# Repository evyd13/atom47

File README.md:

# Atom47

This is the repository for the Atom47. At the moment you'll find Revision 4 AND 5 of the PCB, the final plate file and a design for a 3d printed case.

The Apache2 license apply to all of these works.

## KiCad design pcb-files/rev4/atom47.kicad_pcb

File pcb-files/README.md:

# Atom47 PCB

## Rev5 (with per key RGB)

## Rev4

### JLCPCB order process 

JLCPCB-specific production files can be found in [this folder](/pcb-files/rev4/manufacturing/jlc). Here are the files you need to upload to JLCPCB:

- `atom47-rev4-gerber.zip` 
- `Atom47-Rev4-BOM-JLC.csv` is the BOM (Bill of Materials) file
- `Atom47-Rev4-Bottom-CPL-JLC.csv` is the POS/CPL (Footprint POSition/Component Placement List) file

Once you have the files ready, go to the JLCPCB website and follow the steps below:

1. Upload the gerber file
2. Once it is processed, select the options for the PCB:
   1. Leave all options as default, choose your material and color etc.
   2. Remember that MOQ (Minimum Order Quantity) is `5` PCBs
   3. Set `Confirm Production file` to `Yes`
   4. Enable `PCB Assembly`
   5. Choose `Assemble bottom side`
   6. Leave all options as default, set `Confirm Parts Placement` to `Yes`
   7. Proceed with your order
3. Upload the BOM and CPL files
4. Once the files are uploaded, the system will automatically recognize the components and you will be able to review them:
   1. `ATMEGA32U2` is likely to be out of stock. You can choose the `Do not place` option and source it yourself, then finish assembly by hand 
5. Once the parts list is confirmed, the system will attempt to automatically place the components on the board. The initial placement will be off, but JLCPCB engineers will catch it and fix it for you. You can then review the corrected placement and confirm it later
6. Complete your order:
   1. Pay for production, choose your shipping option etc.
7. Your files will be reviewed by JLCPCB engineers, and you will have to confirm the corrected placement. Here's a preview of the verified, corrected placement:

*Note: MCU not seen here, as this component was out of stock at the time of this order. It was sourced separately, and the assembly was finished by hand*

8. Once you receive your PCBs, you can then proceed with testing, assembly (if needed) and flashing the firmware

### VIA support 

Follow these step to use your Rev4 Atom47 PCB with VIA:

1. Compile the firmware with VIA support using your preferred method
   1. Example: `qmk compile -kb evyd13/atom47 -km via`
2. Flash the firmware using your preferred method
3. Open VIA: 
   1. Navigate to the `Design` tab
   2. Click on `Load` under `Load Draft Definition`
   3. Provide the `Atom47_Rev4.json` file from [this folder](/pcb-files/rev4/via) 
4. Connect your Rev4 Atom47 PCB 

*Note: This definition file only supports the default Vortex Core layout*

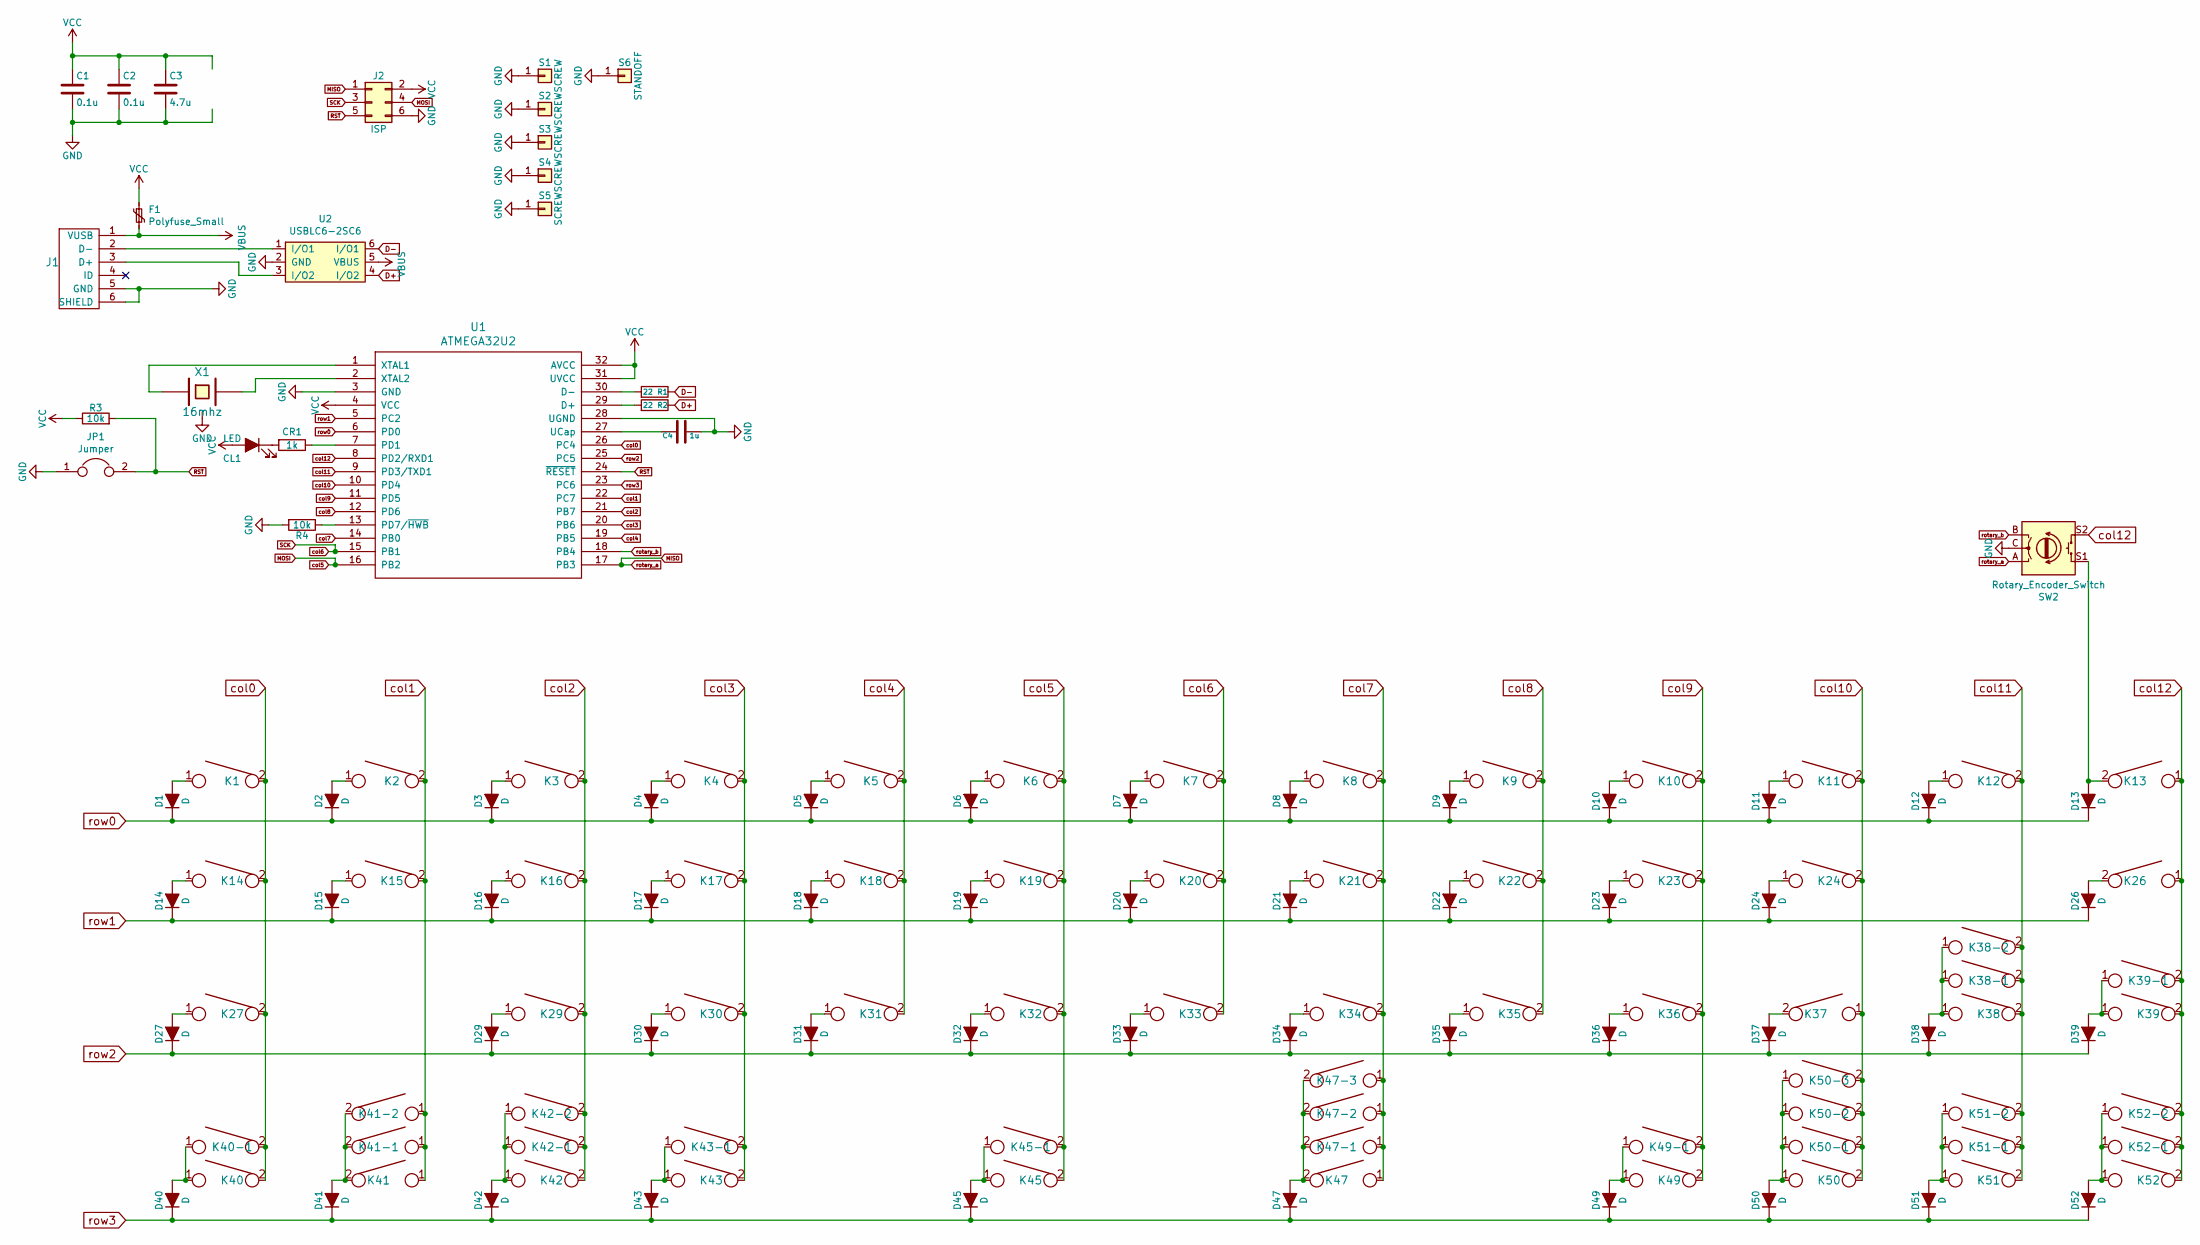
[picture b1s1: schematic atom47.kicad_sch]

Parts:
C1, C2: 0.1u; C_0603
C3: 4.7u; C_0603
C4: 1u; C_0603
CL1: LED; LED_0805
CR1: 1k; R_0603
D1, D2, D3, D4, D5, D6, D7, D8, D9, D10, D11, D12, D13, D14, D15, D16, D17, D18, D19, D20, D21, D22, D23, D24, D26, D27, D29, D30, D31, D32, D33, D34, D35, D36, D37, D38, D39, D40, D41, D42, D43, D45, D47, D49, D50, D51, D52: D; D_0805
F1: Polyfuse_Small; R_0603
J1: USB_mini_micro_B; U-F-M5DD-Y-L
J2: ISP; isp_standard
JP1: Jumper; reset
K1, K2, K3, K4, K5, K6, K7, K8, K9, K10, K11, K12, K13, K15, K16, K17, K18, K19, K20, K21, K22, K23, K24, K29, K30, K31, K32, K33, K34, K35, K36, K37, K38-2, K39, K41, K42, K42-2, K43, K43-1, K49, K49-1, K50, K50-1, K51, K51-1, K52-1: KEYSW; CHERRY_PLATE_100H
K14, K38, K39-1, K40, K41-1, K42-1, K50-3, K51-2, K52: KEYSW; CHERRY_PLATE_125H
K26, K27, K45, K45-1: KEYSW; CHERRY_PLATE_175H
K38-1: KEYSW; CHERRY_PLATE_225H
K40-1, K41-2, K50-2, K52-2: KEYSW; CHERRY_PLATE_150H
K47: KEYSW; CHERRY_PLATE_275H
K47-1: KEYSW; CHERRY_PLATE_625H
K47-2: KEYSW; CHERRY_PLATE_700H
K47-3: KEYSW; CHERRY_PLATE_200H
R1, R2: 22; R_0603
R3, R4: 10k; R_0603
S1, S2, S3, S4, S5: SCREW; Vortex_Core_screw
S6: STANDOFF; vortex_standoff
SW2: Rotary_Encoder_Switch; RotaryEncoder_Alps_EC11
U1: ATMEGA32U2
U2: USBLC6-2SC6
X1: 16mhz; Resonator_SMD_muRata_CSTNExxV-3Pin-p1.2

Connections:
D+: R2.1, U2.4 (I/O2)
D-: R1.1, U2.6 (I/O1)
GND: C1.2, C2.2, C3.2, C4.2, J1.5 (GND), J1.6 (SHIELD), J2.6, JP1.1, R4.2, S1.1, S2.1, S3.1, S4.1, S5.1, S6.1, SW2.C, U1.3 (GND), U1.28 (UGND), U2.2 (GND), X1.3
MISO: J2.1, SW2.A, U1.17 (PB3)
MOSI: J2.4, K6.2, K19.2, K32.2, K45.2, K45-1.2, U1.16 (PB2)
unnamed: C4.1, U1.27 (UCap)
unnamed: CL1.1 (K), CR1.2
unnamed: CR1.1, U1.7 (PD1)
unnamed: D1.2 (A), K1.1
unnamed: D2.2 (A), K2.1
unnamed: D3.2 (A), K3.1
unnamed: D4.2 (A), K4.1
unnamed: D5.2 (A), K5.1
unnamed: D6.2 (A), K6.1
unnamed: D7.2 (A), K7.1
unnamed: D8.2 (A), K8.1
unnamed: D9.2 (A), K9.1
unnamed: D10.2 (A), K10.1
unnamed: D11.2 (A), K11.1
unnamed: D12.2 (A), K12.1
unnamed: D13.2 (A), K13.2, SW2.S1
unnamed: D14.2 (A), K14.1
unnamed: D15.2 (A), K15.1
unnamed: D16.2 (A), K16.1
unnamed: D17.2 (A), K17.1
unnamed: D18.2 (A), K18.1
unnamed: D19.2 (A), K19.1
unnamed: D20.2 (A), K20.1
unnamed: D21.2 (A), K21.1
unnamed: D22.2 (A), K22.1
unnamed: D23.2 (A), K23.1
unnamed: D24.2 (A), K24.1
unnamed: D26.2 (A), K26.2
unnamed: D27.2 (A), K27.1
unnamed: D29.2 (A), K29.1
unnamed: D30.2 (A), K30.1
unnamed: D31.2 (A), K31.1
unnamed: D32.2 (A), K32.1
unnamed: D33.2 (A), K33.1
unnamed: D34.2 (A), K34.1
unnamed: D35.2 (A), K35.1
unnamed: D36.2 (A), K36.1
unnamed: D37.2 (A), K37.2
unnamed: D38.2 (A), K38.1, K38-1.1, K38-2.1
unnamed: D39.2 (A), K39.1, K39-1.1
unnamed: D40.2 (A), K40.1, K40-1.1
unnamed: D41.2 (A), K41.2, K41-1.2, K41-2.2
unnamed: D42.2 (A), K42.1, K42-1.1, K42-2.1
unnamed: D43.2 (A), K43.1, K43-1.1
unnamed: D45.2 (A), K45.1, K45-1.1
unnamed: D47.2 (A), K47.2, K47-1.2, K47-2.2, K47-3.2
unnamed: D49.2 (A), K49.1, K49-1.1
unnamed: D50.2 (A), K50.1, K50-1.1, K50-2.1, K50-3.1
unnamed: D51.2 (A), K51.1, K51-1.1, K51-2.1
unnamed: D52.2 (A), K52.1, K52-1.1, K52-2.1
unnamed: J1.2 (D-), U2.1 (I/O1)
unnamed: J1.3 (D+), U2.3 (I/O2)
unnamed: R1.2, U1.30 (D-)
unnamed: R2.2, U1.29 (D+)
unnamed: R4.1, U1.13 (PD7/~HWB)
unnamed: U1.1 (XTAL1), X1.1
unnamed: U1.2 (XTAL2), X1.2
RST: J2.5, JP1.2, R3.2, U1.24 (~RESET)
SCK: J2.3, K7.2, K20.2, K33.2, U1.15 (PB1)
VBUS: F1.2, J1.1 (VUSB), U2.5 (VBUS)
VCC: C1.1, C2.1, C3.1, CL1.2 (A), F1.1, J2.2, R3.1, U1.4 (VCC), U1.31 (UVCC), U1.32 (AVCC)
col0: K1.2, K14.2, K27.2, K40.2, K40-1.2, U1.26 (PC4)
col1: K2.2, K15.2, K41.1, K41-1.1, K41-2.1, U1.22 (PC7)
col2: K3.2, K16.2, K29.2, K42.2, K42-1.2, K42-2.2, U1.21 (PB7)
col3: K4.2, K17.2, K30.2, K43.2, K43-1.2, U1.20 (PB6)
col4: K5.2, K18.2, K31.2, U1.19 (PB5)
col7: K8.2, K21.2, K34.2, K47.1, K47-1.1, K47-2.1, K47-3.1, U1.14 (PB0)
col8: K9.2, K22.2, K35.2, U1.12 (PD6)
col9: K10.2, K23.2, K36.2, K49.2, K49-1.2, U1.11 (PD5)
col10: K11.2, K24.2, K37.1, K50.2, K50-1.2, K50-2.2, K50-3.2, U1.10 (PD4)
col11: K12.2, K38.2, K38-1.2, K38-2.2, K51.2, K51-1.2, K51-2.2, U1.9 (PD3/TXD1)
col12: K13.1, K26.1, K39.2, K39-1.2, K52.2, K52-1.2, K52-2.2, SW2.S2, U1.8 (PD2/RXD1)
rotary_b: SW2.B, U1.18 (PB4)
row0: D1.1 (K), D2.1 (K), D3.1 (K), D4.1 (K), D5.1 (K), D6.1 (K), D7.1 (K), D8.1 (K), D9.1 (K), D10.1 (K), D11.1 (K), D12.1 (K), D13.1 (K), U1.6 (PD0)
row1: D14.1 (K), D15.1 (K), D16.1 (K), D17.1 (K), D18.1 (K), D19.1 (K), D20.1 (K), D21.1 (K), D22.1 (K), D23.1 (K), D24.1 (K), D26.1 (K), U1.5 (PC2)
row2: D27.1 (K), D29.1 (K), D30.1 (K), D31.1 (K), D32.1 (K), D33.1 (K), D34.1 (K), D35.1 (K), D36.1 (K), D37.1 (K), D38.1 (K), D39.1 (K), U1.25 (PC5)
row3: D40.1 (K), D41.1 (K), D42.1 (K), D43.1 (K), D45.1 (K), D47.1 (K), D49.1 (K), D50.1 (K), D51.1 (K), D52.1 (K), U1.23 (PC6)

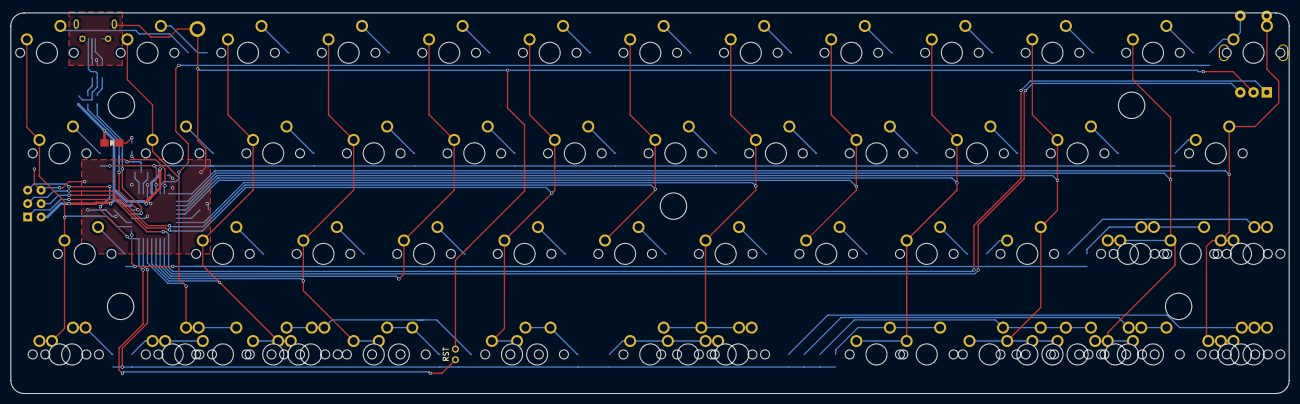
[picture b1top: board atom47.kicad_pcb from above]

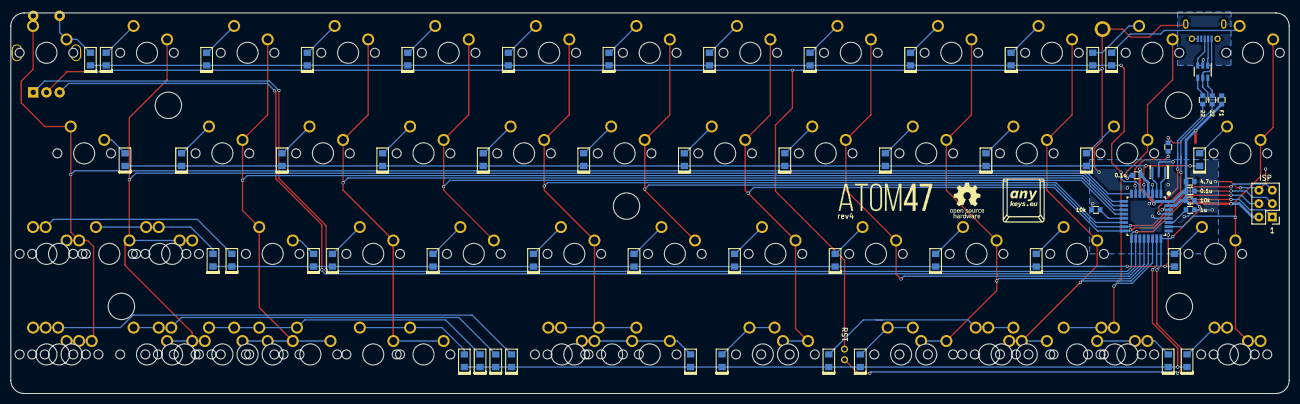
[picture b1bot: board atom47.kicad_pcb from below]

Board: 2 copper layers, 242.2 x 72.1 mm, 139 parts (63 on the bottom side), 82 nets.

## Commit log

2020-06-01 First upload
2020-06-01 was not png but jpg
2021-02-24 Upload PCB/plate files
2022-02-20 Rename pcb-files to pcb-files/rev4
    pcb revs get their own folders
2022-02-20 Upload rev5 files
2022-02-20 Ignore backups
2022-02-20 Update/add readme
2022-03-01 Upload rev5-c files
2022-03-01 Change folder name for rev5-c
2024-02-14 Rev4: Add JLCPCB, VIA files and instructions
